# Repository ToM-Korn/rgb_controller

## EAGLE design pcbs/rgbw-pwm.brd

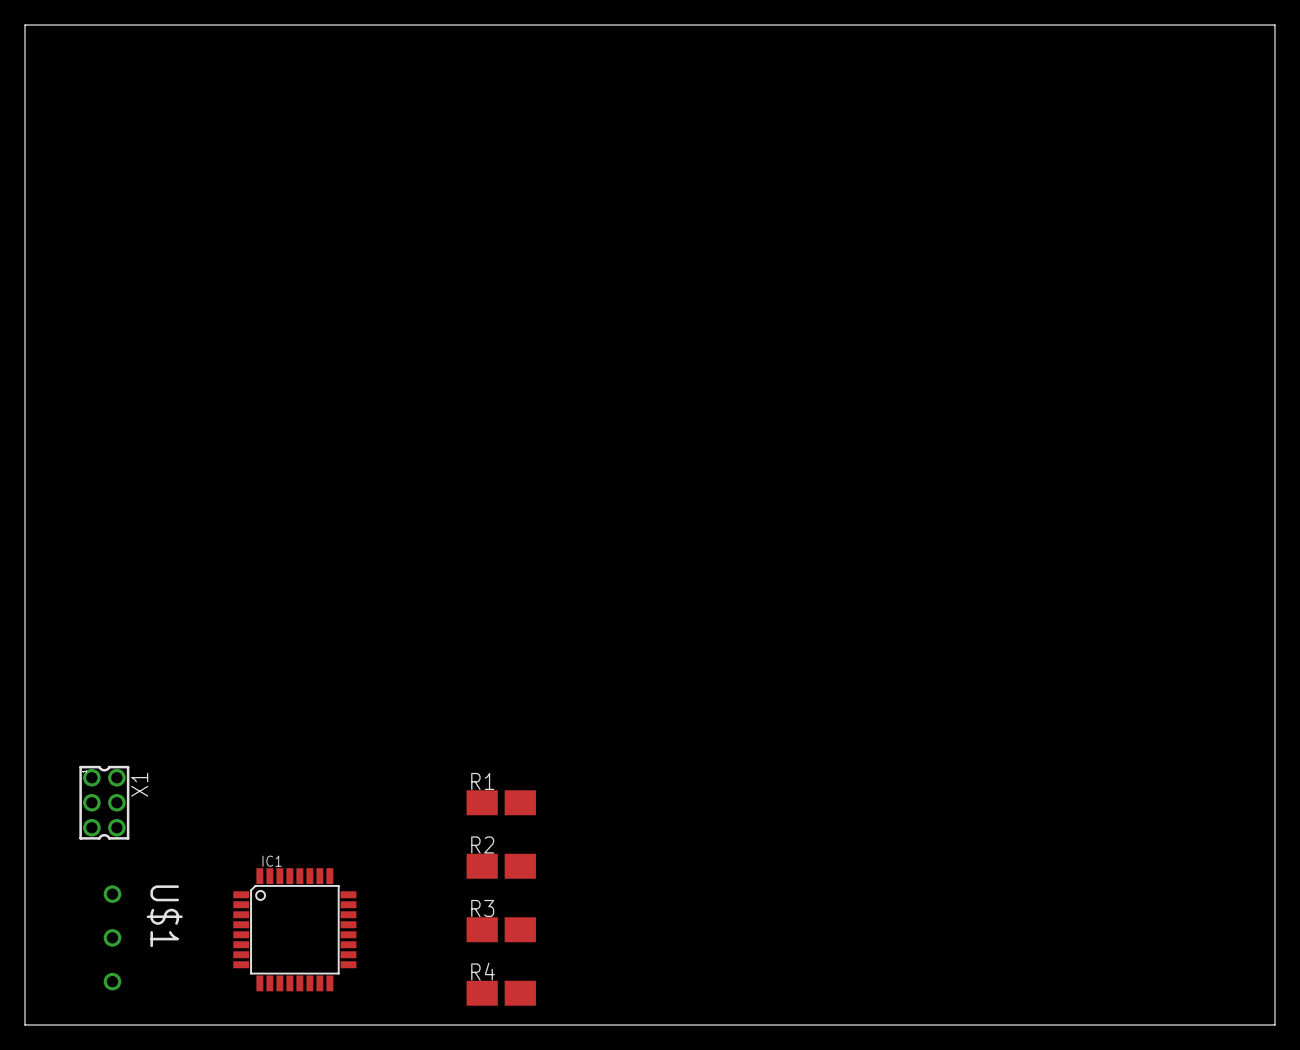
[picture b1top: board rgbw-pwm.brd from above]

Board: 2 copper layers, 100.0 x 80.0 mm, 7 parts (0 on the bottom side), 2 nets, no tracks yet.

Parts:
IC1: MEGA8-AI; TQFP32-08
R1, R2, R3, R4: SMK
U$1: 20020110-C031A01LF
X1: 332-06

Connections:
GND: IC1.3, IC1.5, IC1.21
VCC: IC1.4, IC1.6

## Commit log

2013-04-10 start
2013-04-18 different tests
    with own code / with cyz code
2013-05-05 some more tests
2013-05-14 testing different ws2801 libs
